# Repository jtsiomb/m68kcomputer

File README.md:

Homebrew 68k computer project 1
===============================

About
-----
The purpose of this project is to design a minimal but useful homebrew computer,
based on the Motorola 68010 16/32-bit processor.

The current hardware design is broken into a main processor board, and an I/O
and expansion board with an AVR microcontroller playing the role of UART, timer,
and RTC all in one.

Directory structure:

  * `hw` - hardware: kicad files and pdf schematics.
  * `fw_iolite` - firmware for the I/O controller.
  * `monitor` - ROM monitor program.

Project website: http://nuclear.mutantstargoat.com/hw/m68kcomp1

License
-------
Copyright (C) 2017 John Tsiombikas <nuclear@member.fsf.org>

You are free to use, reproduce, modify, redistribute any parts of this project,
provided you make any derivative work you release, freely available under the
same terms.

More specifically the hardware parts of this project are released under the
Creative Commons Attribution Share-Alike license (see `LICENSE.hw`
for details), and the software/firmware parts are released under the GNU General
Public License v3, or later (see `LICENSE.sw` for details).

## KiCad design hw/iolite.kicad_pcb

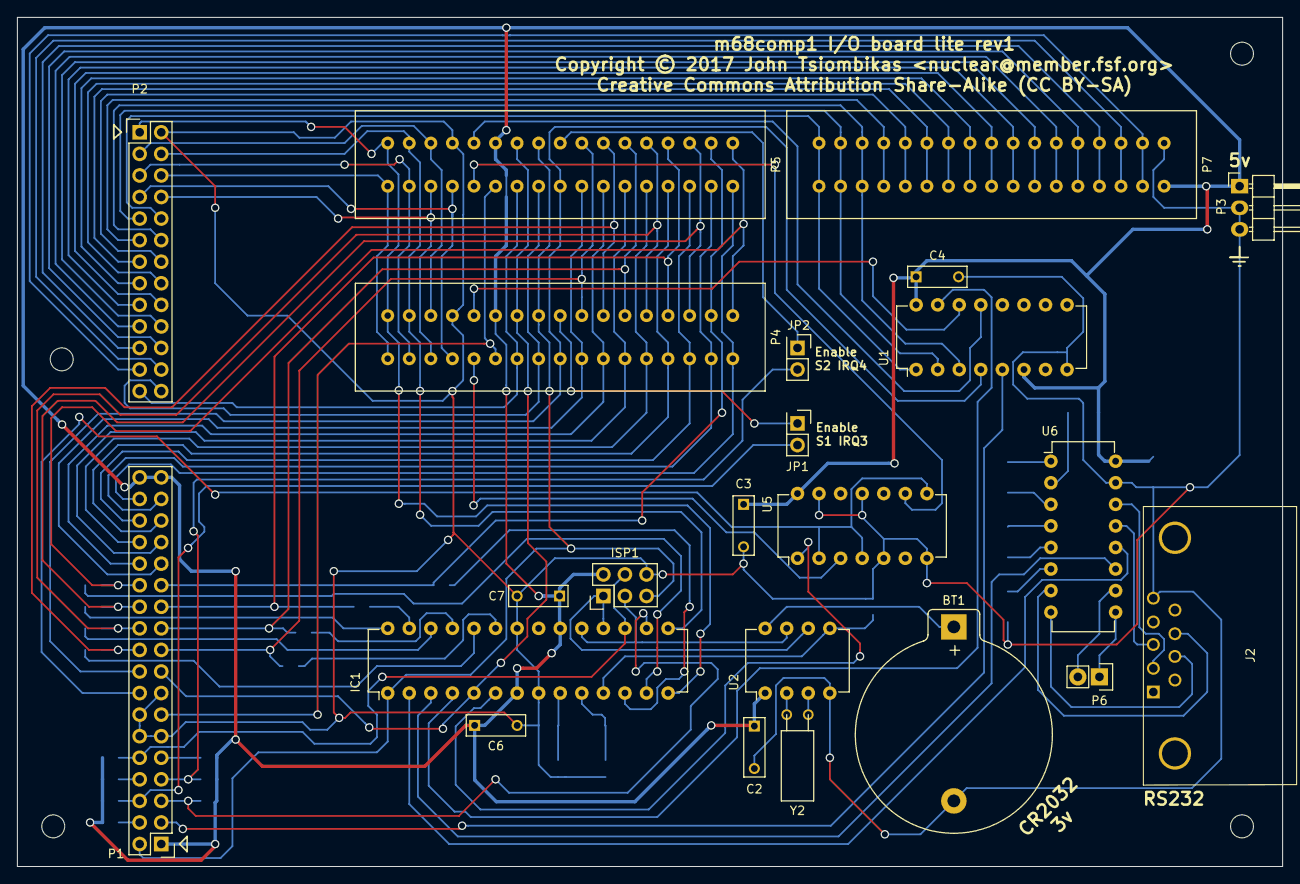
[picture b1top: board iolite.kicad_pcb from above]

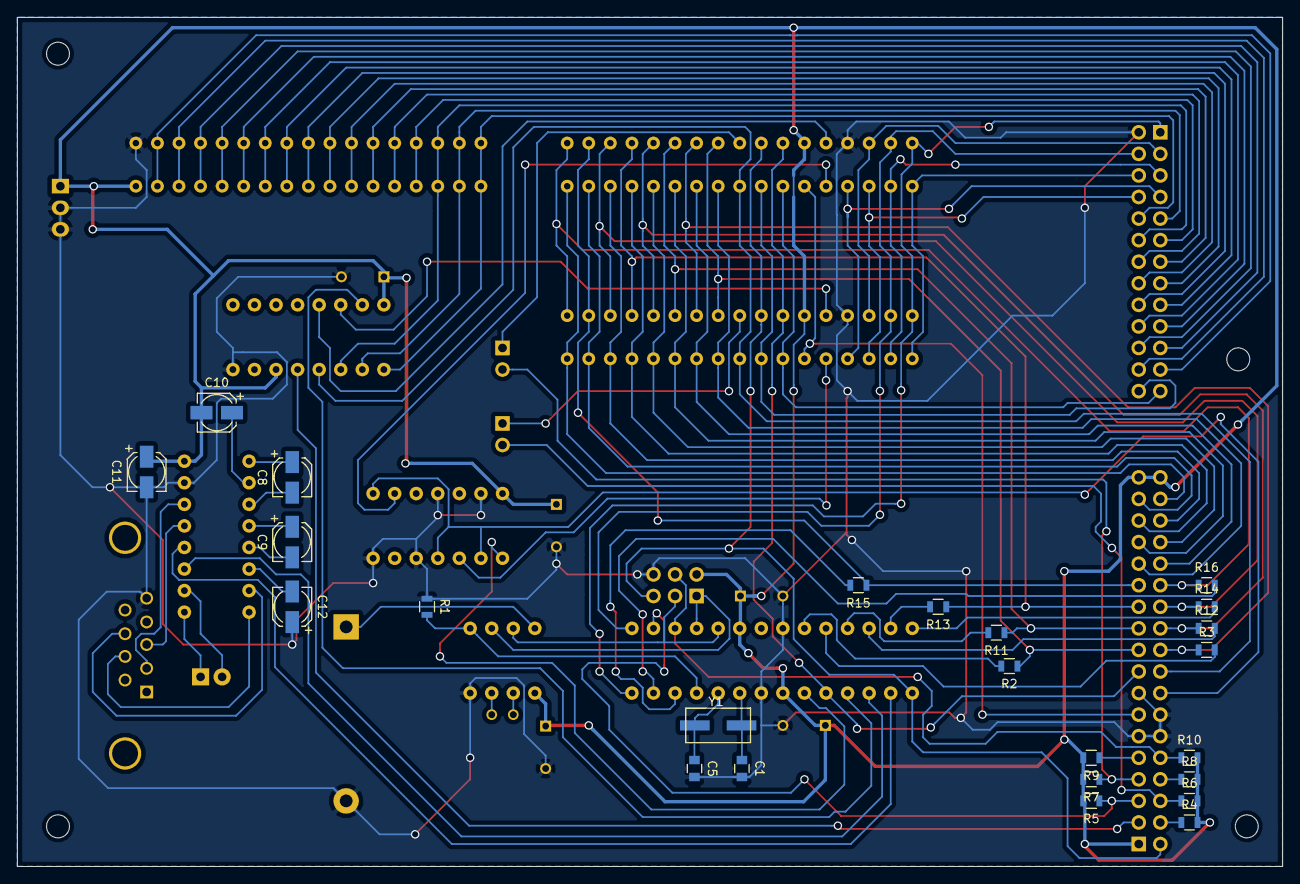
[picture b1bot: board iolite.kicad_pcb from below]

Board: 2 copper layers, 149.0 x 100.0 mm, 47 parts (24 on the bottom side), 94 nets.

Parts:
BT1: 3v; CR2032_CoinCell
C1, C5: 22pF; C_0805
C2, C3, C4, C6, C7: 0.1uF; C_Rect_L7_W2.5_P5
C8, C9, C10, C11, C12: 1uF; c_elec_4x5.7
IC1: ATMEGA168-P; DIP-28_W7.62mm
ISP1: AVR_ISP; Pin_Header_Straight_2x03
J2: DB9; DB9MC
JP1: INT_S1; Pin_Header_Straight_2x01
JP2: INT_S2; Pin_Header_Straight_2x01
P1: CONN_CTL_DATA; Pin_Header_Straight_2x18
P2: CONN_ADDR; Pin_Header_Straight_2x13
P3: SLOT_PWR; Pin_Header_Angled_1x03
P4: SLOT1; edgecon_2x17
P5: SLOT2; edgecon_2x17
P6: CONN_01X02; Pin_Header_Straight_1x02
P7: SLOT_EX_ADDR; edgecon_2x17
R1, R4, R5, R6, R7, R8, R9, R10: 4.7k; R_0805
R2, R3, R11, R12, R13, R14, R15, R16: 120R; R_0805
U1: 74LS138; DIP-16_W7.62mm
U2: DS1302; DIP-8_W7.62mm
U5: 74HC05; DIP-14_W7.62mm
U6: MAX232; DIP-16_W7.62mm
Y1: 14.7456M; crystal_smd_7.6x4.1
Y2: 32.768K; Crystal_Watch

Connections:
/A1: IC1.14, P2.1, P4.2, P5.2
/A2: IC1.15, P2.4, P4.4, P5.4
/A3: P2.3, P4.6, P5.6
/A4: P2.6, P4.1, P5.1
/A5: P2.5, P4.3, P5.3
/A6: P2.8, P4.5, P5.5
/A7: P2.7, P4.7, P5.7
/A8: P2.10, P7.1, P7.2, U1.1
/A9: P2.9, P7.3, P7.4, U1.2
/A10: P2.12, P7.5, P7.6, U1.3
/A11: P2.11, P7.7, P7.8
/A12: P2.14, P7.9, P7.10
/A13: P2.13, P7.11, P7.12
/A14: P2.16, P7.13, P7.14
/A15: P2.15, P7.15, P7.16
/A16: P2.18, P7.17, P7.18
/A17: P2.17, P7.19, P7.20
/A18: P2.20, P7.21, P7.22
/A19: P2.19, P7.23, P7.24
/A20: P2.22, P7.25, P7.26
/A21: P2.21, P7.27, P7.28
/A22: P2.24, P7.29, P7.30
/A23: P2.23, P7.31, P7.32
/BUS0: P1.19, P4.20, P5.20, R2.1
/BUS1: P1.20, P4.22, P5.22, R3.1
/BUS2: P1.21, P4.24, P5.24, R11.1
/BUS3: P1.22, P4.26, P5.26, R12.1
/BUS4: P1.23, P4.28, P5.28, R13.1
/BUS5: P1.24, P4.30, P5.30, R14.1
/BUS6: P1.25, P4.32, P5.32, R15.1
/BUS7: P1.26, P4.34, P5.34, R16.1
/BUS8: P1.27, P4.19, P5.19
/BUS9: P1.28, P4.21, P5.21
/BUS10: P1.29, P4.23, P5.23
/BUS11: P1.30, P4.25, P5.25
/BUS12: P1.31, P4.27, P5.27
/BUS13: P1.32, P4.29, P5.29
/BUS14: P1.33, P4.31, P5.31
/BUS15: P1.34, P4.33, P5.33
/CLK20: P1.13, P4.11, P5.11
/CTS: P6.2, U6.10
/D0: IC1.23, R2.2
/D1: IC1.24, R3.2
/D2: IC1.25, R11.2
/D3: IC1.26, R12.2
/D4: IC1.27, R13.2
/D5: IC1.28, R14.2
/D6: IC1.12, R15.2
/D7: IC1.13, R16.2
/DTACK: IC1.6, U5.1
/DTACK_S1: P4.9, U5.3
/DTACK_S2: P5.9, U5.9
/MISO: IC1.18, ISP1.1, U2.6
/RS232_CTS: J2.8, U6.7
/RS232_RTS: J2.7, U6.8
/RS232_RX: J2.3, U6.13
/RS232_TX: J2.2, U6.14
/RTC_CE: IC1.11, R1.2, U2.5
/RTS: P6.1, U6.9
/RX: IC1.2, U6.12
/SCK: IC1.19, ISP1.3, U2.7
/TX: IC1.3, U6.11
/XTAL1: C1.1, IC1.9, Y1.1
/XTAL2: C5.1, IC1.10, Y1.2
/~AS: P1.18, P4.17, P5.17, U1.4
/~DTACK: P1.16, U5.2, U5.4, U5.8
/~EN_AVR: IC1.4, U1.15
/~EN_S1: P4.10, U1.14
/~EN_S2: P5.10, U1.13
/~INTS1: JP1.1, P4.18
/~INTS2: JP2.1, P5.18
/~IOEN: P1.3, U1.5
/~IRQ1: P1.4, R4.1
/~IRQ2: IC1.16, P1.5, R5.1
/~IRQ3: JP1.2, P1.6, R6.1
/~IRQ4: JP2.2, P1.7, R7.1
/~IRQ5: P1.8, R8.1
/~IRQ6: P1.9, R9.1
/~IRQ7: IC1.17, ISP1.4, P1.10, R10.1
/~LDS: P2.26, P4.15, P5.15
/~SYS_RESET: IC1.1, ISP1.5, P1.2, P4.16, P5.16
/~UDS: P2.25, P4.13, P5.13
/~WR: IC1.5, P1.17, P4.14, P5.14
GND: BT1.2, C1.2, C2.2, C3.2, C4.2, C5.2, C6.2, C7.2, C11.2, C12.1, IC1.8, IC1.22, ISP1.6, J2.5, P1.11, P1.12, P1.14, P1.15, P2.2, P3.2, P3.3, P4.8, P5.8, P7.34, R1.1, U1.8, U2.4, U5.5, U5.7, U5.11, U5.13, U6.15
unnamed: BT1.1, U2.8
unnamed: C8.1, U6.1
unnamed: C8.2, U6.3
unnamed: C9.1, U6.4
unnamed: C9.2, U6.5
unnamed: C10.1, U6.2
unnamed: C12.2, U6.6
unnamed: U2.2, Y2.1
unnamed: U2.3, Y2.2
VCC: C2.1, C3.1, C4.1, C6.1, C7.1, C10.2, C11.1, IC1.7, IC1.20, ISP1.2, P1.1, P1.35, P1.36, P3.1, P4.12, P5.12, P7.33, R4.2, R5.2, R6.2, R7.2, R8.2, R9.2, R10.2, U1.6, U1.16, U2.1, U5.14, U6.16

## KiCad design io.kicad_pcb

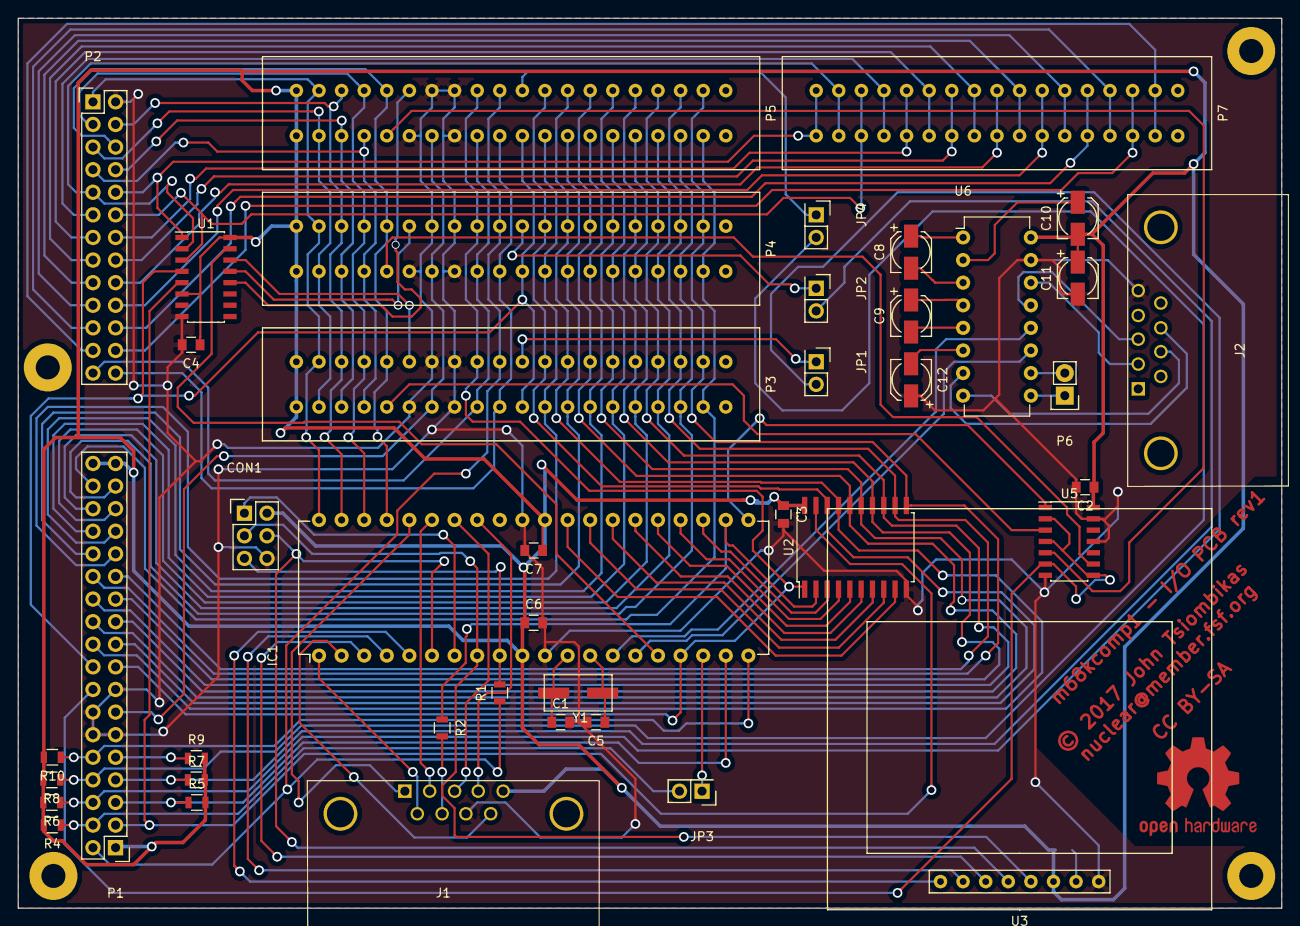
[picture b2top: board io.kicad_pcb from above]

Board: 2 copper layers, 142.0 x 100.0 mm, 43 parts (1 on the bottom side), 107 nets.

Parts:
C1, C5: 22pF; C_0805
C2, C3, C4, C6, C7: 0.1uF; C_0805
C8, C9, C10, C11, C12: 1uF; c_elec_4x5.7
CON1: AVR_ISP; Pin_Header_Straight_2x03
IC1: ATMEGA644P-P; DIP-40_W15.24mm
J1, J2: DB9; DB9MC
JP1: INT_S1; Pin_Header_Straight_2x01
JP2: INT_S2; Pin_Header_Straight_2x01
JP3: PAD_INT; Pin_Header_Straight_2x01
JP4: INT_S3; Pin_Header_Straight_2x01
P1: CONN_CTL_DATA; Pin_Header_Straight_2x18
P2: CONN_ADDR; Pin_Header_Straight_2x13
P3: SLOT1; edgecon_2x20
P4: SLOT2; edgecon_2x20
P5: SLOT3; edgecon_2x20
P6: CONN_01X02; Pin_Header_Straight_1x02
P7: SLOT_EX_ADDR; edgecon_2x17
R1: 1k; R_0805
R2: 120; R_0805
R3: 330; R_0805
R4, R5, R6, R7, R8, R9, R10: 4.7k; R_0805
U1: 74LS138; SOIC-16_3.9x9.9mm_Pitch1.27mm
U2: 74HC245; SOIC-20W_7.5x12.8mm_Pitch1.27mm
U3: DISP_5110; nokia5110lcd
U5: 74HC05; SOIC-14_3.9x8.7mm_Pitch1.27mm
U6: MAX232; DIP-16_W7.62mm
Y1: 14.7456M; crystal_smd_7.6x4.1

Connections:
/A1: IC1.40, P2.1, P3.4, P4.4, P5.4
/A2: IC1.39, P2.4, P3.6, P4.6, P5.6
/A3: IC1.38, P2.3, P3.8, P4.8, P5.8
/A4: IC1.37, P2.6, P3.10, P4.10, P5.10
/A5: P2.5, P3.3, P4.3, P5.3
/A6: P2.8, P3.5, P4.5, P5.5
/A7: P2.7, P3.7, P4.7, P5.7
/A8: P2.10, P7.1, P7.2, U1.1
/A9: P2.9, P7.3, P7.4, U1.2
/A10: P2.12, P7.5, P7.6, U1.3
/A11: P2.11, P7.7, P7.8
/A12: P2.14, P7.9, P7.10
/A13: P2.13, P7.11, P7.12
/A14: P2.16, P7.13, P7.14
/A15: P2.15, P7.15, P7.16
/A16: P2.18, P7.17, P7.18
/A17: P2.17, P7.19, P7.20
/A18: P2.20, P7.21, P7.22
/A19: P2.19, P7.23, P7.24
/A20: P2.22, P7.25, P7.26
/A21: P2.21, P7.27, P7.28
/A22: P2.24, P7.29, P7.30
/A23: P2.23, P7.31, P7.32
/BUS0: P1.19, P3.24, P4.24, P5.24, U2.18
/BUS1: P1.20, P3.26, P4.26, P5.26, U2.17
/BUS2: P1.21, P3.28, P4.28, P5.28, U2.16
/BUS3: P1.22, P3.30, P4.30, P5.30, U2.15
/BUS4: P1.23, P3.32, P4.32, P5.32, U2.14
/BUS5: P1.24, P3.34, P4.34, P5.34, U2.13
/BUS6: P1.25, P3.36, P4.36, P5.36, U2.12
/BUS7: P1.26, P3.38, P4.38, P5.38, U2.11
/BUS8: P1.27, P3.23, P4.23, P5.23
/BUS9: P1.28, P3.25, P4.25, P5.25
/BUS10: P1.29, P3.27, P4.27, P5.27
/BUS11: P1.30, P3.29, P4.29, P5.29
/BUS12: P1.31, P3.31, P4.31, P5.31
/BUS13: P1.32, P3.33, P4.33, P5.33
/BUS14: P1.33, P3.35, P4.35, P5.35
/BUS15: P1.34, P3.37, P4.37, P5.37
/CLK20: P1.13, P3.13, P4.13, P5.13
/CTS: P6.2, U6.10
/D0: IC1.22, R2.1, U2.2
/D1: IC1.23, U2.3
/D2: IC1.24, U2.4
/D3: IC1.25, U2.5
/D4: IC1.26, U2.6
/D5: IC1.27, U2.7
/D6: IC1.28, U2.8
/D7: IC1.29, U2.9
/DM_CE: IC1.4, U3.2
/DM_DC: IC1.3, U3.3
/DM_RST: IC1.5, U3.1
/DTACK: IC1.21, U5.1
/MISO: CON1.1, IC1.7
/MOSI: CON1.4, IC1.6, U3.4
/PAD_AB: IC1.1, J1.6
/PAD_DN: IC1.35, J1.2
/PAD_LEFT: IC1.34, J1.3
/PAD_RIGHT: IC1.33, J1.4
/PAD_SC: IC1.2, J1.9
/PAD_SEL: J1.7, R2.2
/PAD_UP: IC1.36, J1.1
/RS232_CTS: J2.8, U6.7
/RS232_RTS: J2.7, U6.8
/RS232_RX: J2.3, U6.13
/RS232_TX: J2.2, U6.14
/RTS: P6.1, U6.9
/RX: IC1.14, U6.12
/SCK: CON1.3, IC1.8, U3.5
/TX: IC1.15, U6.11
/~AS: P1.18, P3.21, P4.21, P5.21, U1.4
/~AVR_RST: CON1.5, IC1.9, R1.2
/~DTACK: P1.16, U5.2, U5.4, U5.6, U5.8
/~EN_AVR: IC1.16, U1.15
/~EN_S1: P3.12, U1.14
/~EN_S2: P4.12, U1.13
/~EN_S3: P5.12, U1.12
/~INTS1: JP1.1, P3.22
/~INTS2: JP2.1, P4.22
/~INTS3: JP4.1, P5.22
/~IOEN: P1.3, U1.5, U2.19
/~IRQ1: JP3.2, P1.4, R4.1
/~IRQ2: IC1.19, P1.5, R5.1
/~IRQ3: JP1.2, P1.6, R6.1
/~IRQ4: JP2.2, P1.7, R7.1
/~IRQ5: JP4.2, P1.8, R8.1
/~IRQ6: P1.9, R9.1
/~IRQ7: IC1.20, P1.10, R10.1
/~LDS: P2.26, P3.19, P4.19, P5.19
/~PAD_INT: IC1.18, JP3.1
/~SYS_RESET: P1.2, P3.20, P4.20, P5.20, R1.1
/~UDS: P2.25, P3.17, P4.17, P5.17
/~WR: IC1.17, P1.17, P3.18, P4.18, P5.18, U2.1
GND: C1.2, C2.2, C3.2, C4.2, C5.2, C6.2, C7.2, C11.2, C12.1, CON1.6, IC1.11, IC1.31, J1.8, J2.5, P1.11, P1.12, P1.14, P1.15, P2.2, P3.11, P3.14, P3.15, P3.16, P4.11, P4.14, P4.15, P4.16, P5.11, P5.14, P5.15, P5.16, U1.8, U2.10, U3.8, U5.7, U5.11, U5.13, U6.15
unnamed: C1.1, IC1.12, Y1.1
unnamed: C5.1, IC1.13, Y1.2
unnamed: C8.1, U6.1
unnamed: C8.2, U6.3
unnamed: C9.1, U6.4
unnamed: C9.2, U6.5
unnamed: C10.1, U6.2
unnamed: C12.2, U6.6
unnamed: P3.9, U5.3
unnamed: P4.9, U5.9
unnamed: P5.9, U5.5
unnamed: R3.2, U3.7
VCC: C2.1, C3.1, C4.1, C6.1, C7.1, C10.2, C11.1, CON1.2, IC1.10, IC1.30, J1.5, P1.1, P1.35, P1.36, P3.1, P3.2, P4.1, P4.2, P5.1, P5.2, R3.1, R4.2, R5.2, R6.2, R7.2, R8.2, R9.2, R10.2, U1.6, U1.16, U2.20, U3.6, U5.14, U6.16

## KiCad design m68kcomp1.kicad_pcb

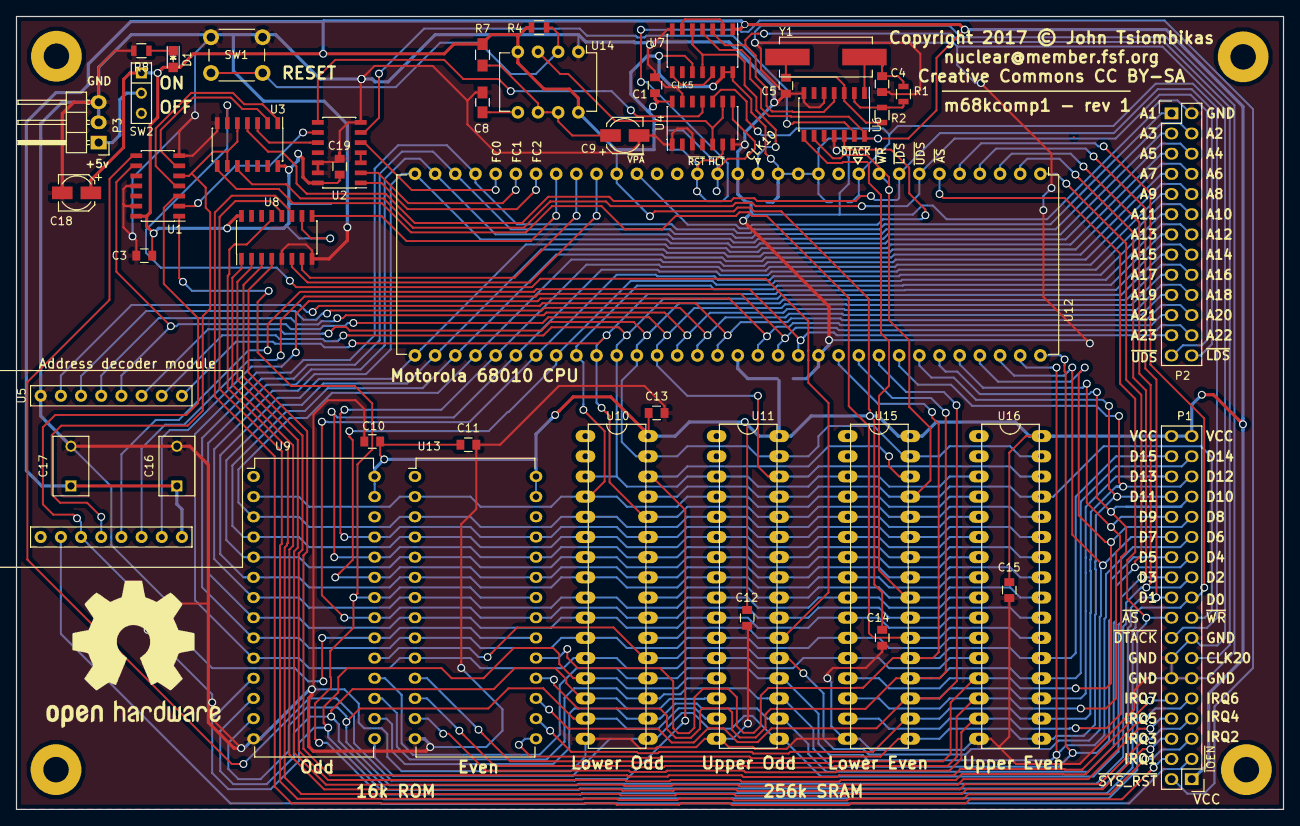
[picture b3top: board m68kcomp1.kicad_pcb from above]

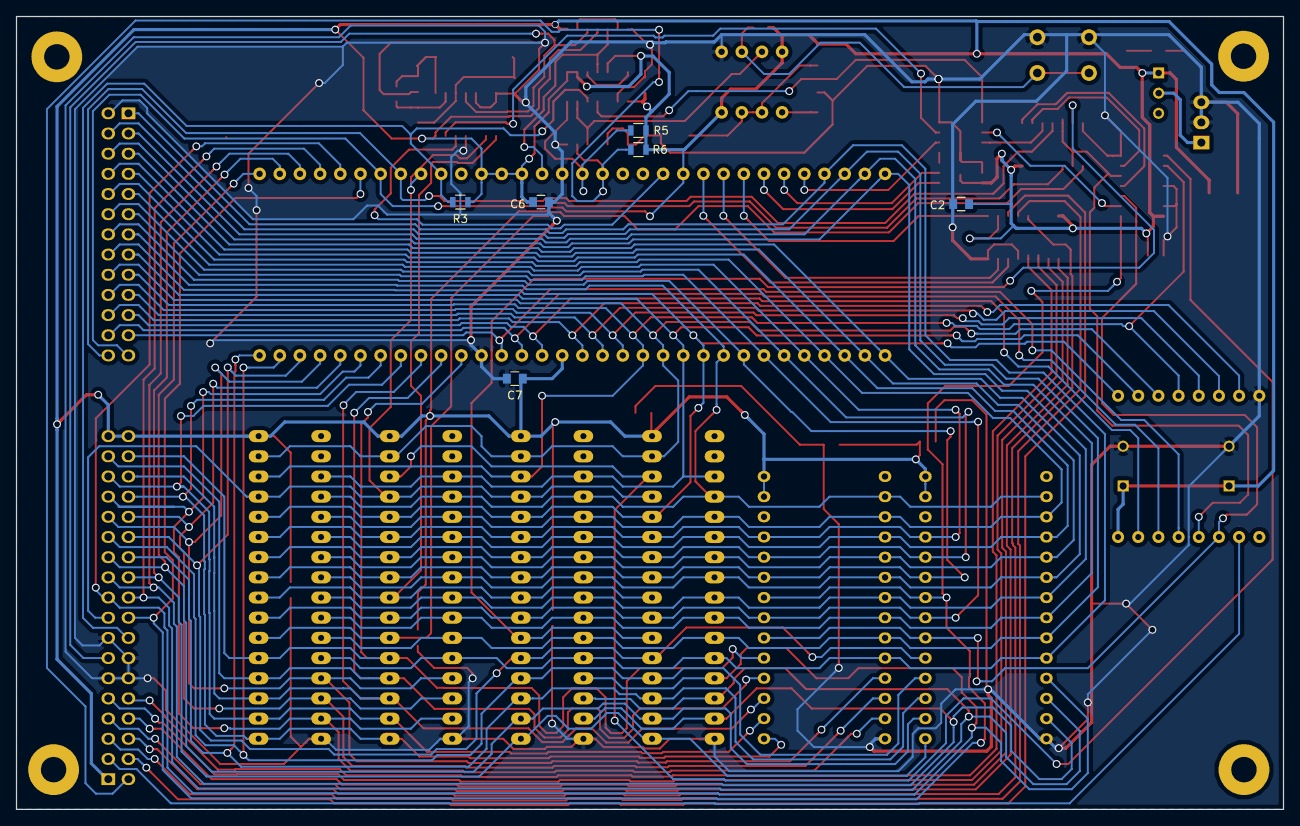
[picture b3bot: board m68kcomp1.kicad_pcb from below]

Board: 2 copper layers, 159.5 x 99.8 mm, 50 parts (6 on the bottom side), 89 nets.

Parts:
C1, C2, C3, C6, C7, C10, C11, C12, C13, C14, C15, C19: 0.1uF; C_0805
C4, C5: 22pF; C_0805
C8: 10nF; C_0805_HandSoldering
C9: 1uF; c_elec_4x5.7
C16, C17: 0.1uF; C_Disc_D7.5_P5
C18: 4.7uF; c_elec_4x5.7
D1: LED; LED_0805
P1: CONN_CTL_DATA; Pin_Header_Straight_2x18
P2: CONN_ADDR; Pin_Header_Straight_2x13_oval
P3: POWER; Pin_Header_Angled_1x03
R1: 47k; R_0805
R2: 120R; R_0805
R3, R4, R5, R6: 4.7k; R_0805
R7: 1M; R_0805_HandSoldering
R8: 330; R_0805
SW1: RST_SW; SW_PUSH_6mm
SW2: PWR_SW; SW_Micro_SPST
U1: 74LS04; SOIC-14_3.9x8.7mm_Pitch1.27mm
U2: 74LS08; SOIC-14_3.9x8.7mm_Pitch1.27mm
U3: 74LS32; SOIC-14_3.9x8.7mm_Pitch1.27mm
U4: 74HC05; SOIC-14_3.9x8.7mm_Pitch1.27mm
U5: address_decoder; addr_dec_module
U6: 74HC04; SOIC-14_3.9x8.7mm_Pitch1.27mm
U7: 74HC74; SOIC-14_3.9x8.7mm_Pitch1.27mm
U8: 74LS148; SOIC-16_3.9x9.9mm_Pitch1.27mm
U9, U13: at28c64; DIP-28_W15.24mm_oval
U10, U11, U15, U16: sram_um61512ak; DIP-32L
U12: 68010D; DIP-64_W22.86mm
U14: NE555; DIP-8_W7.62mm
Y1: 20MHz; Crystal_HC49-SD_SMD

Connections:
/5v: P3.1, SW2.2
/A1: P2.1, U9.10, U10.12, U11.12, U12.29, U13.10, U15.12, U16.12
/A2: P2.4, U9.9, U10.11, U11.11, U12.30, U13.9, U15.11, U16.11
/A3: P2.3, U9.8, U10.10, U11.10, U12.31, U13.8, U15.10, U16.10
/A4: P2.6, U9.7, U10.9, U11.9, U12.32, U13.7, U15.9, U16.9
/A5: P2.5, U9.6, U10.8, U11.8, U12.33, U13.6, U15.8, U16.8
/A6: P2.8, U9.5, U10.7, U11.7, U12.34, U13.5, U15.7, U16.7
/A7: P2.7, U9.4, U10.6, U11.6, U12.35, U13.4, U15.6, U16.6
/A8: P2.10, U9.3, U10.5, U11.5, U12.36, U13.3, U15.5, U16.5
/A9: P2.9, U9.25, U10.27, U11.27, U12.37, U13.25, U15.27, U16.27
/A10: P2.12, U9.24, U10.26, U11.26, U12.38, U13.24, U15.26, U16.26
/A11: P2.11, U9.21, U10.23, U11.23, U12.39, U13.21, U15.23, U16.23
/A12: P2.14, U9.23, U10.25, U11.25, U12.40, U13.23, U15.25, U16.25
/A13: P2.13, U9.2, U10.4, U11.4, U12.41, U13.2, U15.4, U16.4
/A14: P2.16, U5.1, U10.28, U11.28, U12.42, U15.28, U16.28
/A15: P2.15, U5.2, U10.3, U11.3, U12.43, U15.3, U16.3
/A16: P2.18, U5.3, U10.31, U11.31, U12.44, U15.31, U16.31
/A17: P2.17, U1.9, U5.4, U11.30, U12.45, U16.30
/A18: P2.20, U5.5, U12.46
/A19: P2.19, U5.6, U12.47
/A20: P2.22, U5.7, U12.48
/A21: P2.21, U5.15, U12.50
/A22: P2.24, U5.14, U12.51
/A23: P2.23, U5.13, U12.52
/AS: U1.2, U2.9
/CLK10: U7.5, U7.11, U12.15
/CLK20: P1.13, U6.4, U7.3
/D0: P1.19, U9.11, U10.13, U11.13, U12.5
/D1: P1.20, U9.12, U10.14, U11.14, U12.4
/D2: P1.21, U9.13, U10.15, U11.15, U12.3
/D3: P1.22, U9.15, U10.17, U11.17, U12.2
/D4: P1.23, U9.16, U10.18, U11.18, U12.1
/D5: P1.24, U9.17, U10.19, U11.19, U12.64
/D6: P1.25, U9.18, U10.20, U11.20, U12.63
/D7: P1.26, U9.19, U10.21, U11.21, U12.62
/D8: P1.27, U12.61, U13.11, U15.13, U16.13
/D9: P1.28, U12.60, U13.12, U15.14, U16.14
/D10: P1.29, U12.59, U13.13, U15.15, U16.15
/D11: P1.30, U12.58, U13.15, U15.17, U16.17
/D12: P1.31, U12.57, U13.16, U15.18, U16.18
/D13: P1.32, U12.56, U13.17, U15.19, U16.19
/D14: P1.33, U12.55, U13.18, U15.20, U16.20
/D15: P1.34, U12.54, U13.19, U15.21, U16.21
/FC0: U2.5, U12.28
/FC1: U2.2, U12.27
/FC2: U2.1, U12.26
/IPL0: U8.9, U12.25
/IPL1: U8.7, U12.24
/IPL2: U8.6, U12.23
/RAMEN: U1.6, U3.2
/ROMEN: U1.4, U3.1
/~AS: P1.18, U1.1, U9.22, U12.6, U13.22
/~IOEN: P1.3, U5.10
/~RAMEN: U1.5, U3.5, U3.9, U5.12
/~RD: U6.8, U10.24, U11.24, U15.24, U16.24
/~ROMEN: U1.3, U5.11, U9.20, U13.20
/~VPA: U6.12, U12.21
/~WR: P1.17, U6.9, U10.29, U11.29, U12.9, U15.29, U16.29
GND: C1.2, C2.2, C3.2, C4.2, C5.2, C6.2, C7.2, C8.2, C9.2, C10.2, C11.2, C12.2, C13.2, C14.2, C15.2, C16.2, C17.2, C18.2, C19.2, P1.11, P1.12, P1.14, P1.15, P2.2, P3.2, P3.3, R8.2, SW1.1, U1.7, U1.11, U1.13, U2.7, U2.12, U2.13, U3.7, U4.1, U4.3, U4.7, U4.13, U5.8, U6.5, U6.7, U6.11, U7.7, U8.5, U8.8, U9.14, U10.16, U11.16, U12.16, U12.53, U13.14, U14.1, U15.16, U16.16
unnamed: C4.1, R1.2, U6.1, Y1.1
unnamed: C5.1, R2.2, U6.3, Y1.2
unnamed: C8.1, U14.5
unnamed: C9.1, R7.1, U14.6, U14.7
unnamed: D1.1, R8.1
unnamed: R1.1, R2.1, U6.2
unnamed: R4.2, SW1.2, U14.2
unnamed: R5.2, U4.8, U12.17
unnamed: U1.8, U10.30, U15.30
unnamed: U2.3, U2.4
unnamed: U2.6, U6.13
unnamed: U2.8, U4.11
unnamed: U2.10, U3.3
unnamed: U7.2, U7.6
unnamed: U7.8, U7.12
unnamed: U3.6, U10.22, U11.22
unnamed: U4.5, U4.9, U14.3
unnamed: U3.8, U15.22, U16.22
VCC: C1.1, C2.1, C3.1, C6.1, C7.1, C10.1, C11.1, C12.1, C13.1, C14.1, C15.1, C16.1, C17.1, C18.1, C19.1, D1.2, P1.1, P1.35, P1.36, R3.1, R4.1, R5.1, R6.2, R7.2, SW2.1, U1.14, U2.14, U3.14, U4.14, U5.16, U6.14, U7.1, U7.4, U7.10, U7.13, U7.14, U8.10, U8.16, U9.27, U9.28, U10.32, U11.32, U12.12, U12.13, U12.14, U12.22, U12.49, U13.27, U13.28, U14.4, U14.8, U15.32, U16.32
~DTACK: P1.16, R3.2, U4.10, U12.10
~IRQ1: P1.4, U8.11
~IRQ2: P1.5, U8.12
~IRQ3: P1.6, U8.13
~IRQ4: P1.7, U8.1
~IRQ5: P1.8, U8.2
~IRQ6: P1.9, U8.3
~IRQ7: P1.10, U8.4
~LDS: P2.26, U3.4, U12.8
~SYS_RESET: P1.2, R6.1, U4.6, U12.18
~UDS: P2.25, U3.10, U12.7

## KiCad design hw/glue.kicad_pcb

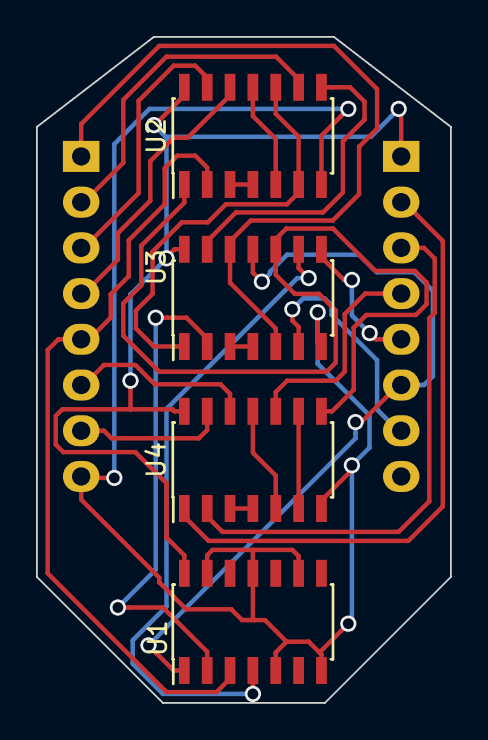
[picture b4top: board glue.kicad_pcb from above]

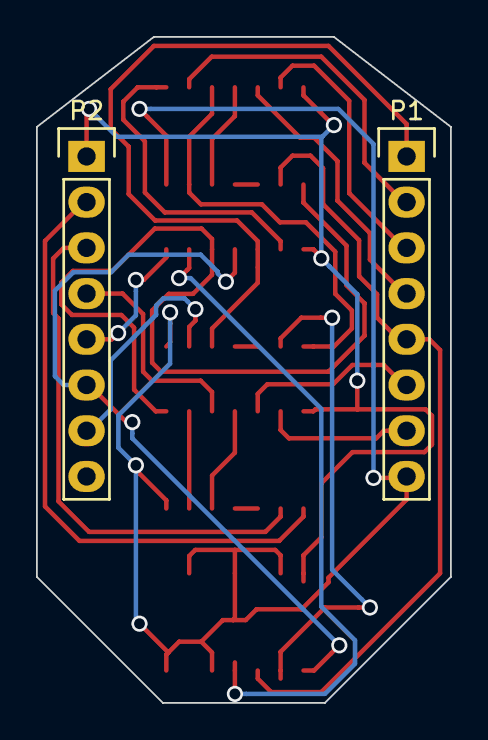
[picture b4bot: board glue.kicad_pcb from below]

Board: 2 copper layers, 23.0 x 37.0 mm, 6 parts (2 on the bottom side), 26 nets.

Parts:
P1, P2: CONN_01X08; Pin_Header_Straight_1x08
U1: 74LS04; SOIC-14_3.9x8.7mm_Pitch1.27mm
U2, U3, U4: 74LS32; SOIC-14_3.9x8.7mm_Pitch1.27mm

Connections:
/A14: P1.1, U3.5, U3.12
/A15: P1.2, U2.9
/A16: P1.3, U2.13
/A17: P1.4, U2.12
/A18: P1.5, U1.3, U2.2
/A19: P1.6, U4.12
/A20: P1.7, U4.13
/A21: P2.2, U4.1
/A22: P2.3, U4.2
/A23: P2.4, U4.10
/~EN32: U2.8, U3.13
/~EN64: U2.6, U2.10, U3.1
/~EN512: U2.1, U3.10, U4.8
/~IOEN: P2.7, U3.6
/~RAMEN: P2.5, U3.8
/~ROMEN: P2.6, U1.1, U3.11
GND: P1.8, U1.5, U1.7, U1.9, U1.11, U1.13, U2.7, U3.7, U4.7
unnamed: U1.2, U3.2
unnamed: U1.4, U3.9
unnamed: U2.3, U2.4
unnamed: U2.5, U2.11
unnamed: U3.3, U3.4
unnamed: U4.3, U4.4
unnamed: U4.6, U4.9
unnamed: U4.5, U4.11
VCC: P2.1, U1.14, U2.14, U3.14, U4.14

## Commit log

2017-03-04 DRAM changes
2017-03-07 dram controller *might* work
2017-03-07 forgot to add the dram controller circuit
2017-03-14 static low ram
2017-03-17 moving along
2017-03-17 laying out the board
2017-03-18 holy shit laying out this PCB takes a lot of time
2017-03-18 pcb layout almost done
2017-03-19 completed pcb layout
2017-03-19 changes for manufacture
2017-03-19 added schematic pdf
2017-03-20 started on the I/O board
2017-03-20 I/O board schematic done
2017-03-21 io board pcb layout in progress
2017-03-23 new layout
2017-03-23 added gerbers dir to .hgignore
2017-03-23 layout progresses
2017-03-24 I/O PCB almost done
2017-03-24 mostly done
2017-03-24 increased the via pad size
2017-03-28 io lite
2017-03-31 updated schematics
2017-04-01 changed directory structured, moved everything into hw/ to prepare for merging the software part in the same repo
2017-04-01 added the software part
2017-04-01 added readme and license files
2017-04-02 interrupts working, UART transmit/receive (receive works only with word sizes)
2017-04-03 found the byte-transfer bug. Need to use odd I/O addresses the way I wired up the AVR in the I/O board
2017-04-03 changed the data bus hookup to the AVR microcontroller, to use the upper data lines instead of the lower ones.
2017-04-05 updated readme and renamed test.s
2017-04-05 writing the ROM monitor
2017-04-05 writing the monitor
2017-04-06 debugging the ROM monitor
2017-04-06 monitor commands seem to work fine now
2017-04-06 removed debug code, and added exec status in cmd_exec
2017-04-06 ops, changed the UART buffer size for debugging and forgot to also change the wrap-around mask
2017-04-06 as a matter of fact, let's make the mask (SZ - 1) to avoid similar problems in the future
2017-04-06 renamed test2 to monitor
2017-04-06 updated the readme file
2017-04-07 added bin2moncmd tool
2017-04-07 debugging intermittent I/O DTACK issue
2017-04-07 fixed monitor input handling, and cmd_write bug
2017-04-07 updated schematic
2017-04-07 added loadable test program
2017-04-07 converting \n -> \r\n in printstr
2017-04-08 testprog1 (C)
2017-04-09 koch snowflake
2017-04-09 removed extraneous include
2017-04-09 changed default UART speed to 115200
2017-04-09 removed some redundant newlines from ReGIS code
2017-04-09 reorganized test progs in their own directory, and added 3dcube_regis
2017-04-09 - fixed program names in test program makefiles - made the koch curve draw visibly (but more slowly)
2017-04-13 zardoz
2017-04-14 writing zardoz command parser and editing
2017-04-15 editing almost works, need to send the appropriate commands to the terminal
2017-04-15 terminal control
2017-04-22 notes for ideas about a simple MMU to support a UNIX-like kernel
2017-04-29 added the project website to the readme file
2018-01-03 fw_iolite: added write handler to set the RTC through command/data register writes
2018-02-03 added RTC test program
2018-02-03 updated the firmware to correctly handle RTC read/write requests from the processor

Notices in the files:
hw/iolite.kicad_pcb:
Copyright © 2017 John Tsiombikas
Creative Commons Attribution Share-Alike (CC BY-SA)
io.kicad_pcb:
CC BY-SA
m68kcomp1.kicad_pcb:
Copyright 2017 © John Tsiombikas
Creative Commons CC BY-SA
